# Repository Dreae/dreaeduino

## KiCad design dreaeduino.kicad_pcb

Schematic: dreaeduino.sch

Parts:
C1, C2: 22 pF; C_0805_2012Metric; PartNumber 885012007012
C3, C4: 10uF; C_0805_2012Metric; PartNumber CC0805ZKY5V6BB106
C5: 10uF; C_1210_3225Metric; PartNumber TAJB106K006TNJ
C6: 0.1 uF; C_0805_2012Metric; PartNumber 885012207098
D1: LED; LED_0805_2012Metric_Castellated; PartNumber 150080GS75000
J1, J2, J3, J4: Conn_01x08_Female; PinHeader_1x08_P2.54mm_Vertical
J5: USB_B_Micro; USB_Micro-B_Molex-105017-0001; PartNumber 105017-0001
J6, J7: Conn_02x03_Odd_Even; PinHeader_2x03_P2.54mm_Vertical; PartNumber 61200621621
R1: 10k; R_0805_2012Metric; PartNumber ERJ-6ENF1002V
R2: 220; R_0805_2012Metric; PartNumber CRCW0805220RFKEB
SW1: SW_DIP_x01; SW_SPST_TL3305A; PartNumber TL3305AF160QG
U1: ATxmega32A4U-AU; TQFP-44_10x10mm_P0.8mm; PartNumber ATxmega32A4-AU
U2: TXB0104D; SOIC-14_3.9x8.7mm_P1.27mm; PartNumber TXB0104D
U3: NCP1117ST33T3G; SOT-223; MPN NCP1117ST33T3G; Digi-Key_PN NCP1117ST33T3GOSCT-ND
Y1: 32 MHz; Crystal_SMD_2520-4Pin_2.5x2.0mm; PartNumber FA-20H 32.0000MF20X-K3

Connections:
+5V: C3.1, C5.1, J5.1, J7.2, U2.14, U3.3
/PB0: J1.4, U1.4 (AREFB/PB0)
/PB1: J1.3, U1.5 (PB1)
/PB2: J1.2, U1.6 (PB2)
/PB3: J1.1, U1.7 (PB3)
/PE0: J1.8, U1.28 (PE0)
/PE1: J1.7, U1.29 (PE1)
/PE2: J1.6, U1.32 (PE2)
/PE3: J1.5, U1.33 (PE3)
/Reset: J6.5, R1.2, SW1.2, U1.35 (~RESET~/PDI_CLK), U2.2
GND: C1.2, C2.2, C3.2, C4.2, C5.2, C6.1, J5.5, J6.6, J7.6, R2.1, SW1.1, U1.8 (GND), U1.18 (GND), U1.30 (GND), U1.38 (GND), U2.7, U3.1
unnamed: C1.1, U1.36 (PR0/XTAL2), Y1.1
unnamed: C2.1, U1.37 (PR1/XTAL1), Y1.3
unnamed: D1.1, R2.2
unnamed: J2.1, U1.27 (PD7)
unnamed: J2.2, U1.26 (PD6)
unnamed: J2.3, U1.25 (PD5)
unnamed: J2.4, U1.24 (PD4)
unnamed: J2.5, U1.23 (PD3)
unnamed: J2.6, U1.22 (PD2)
unnamed: J2.7, U1.21 (PD1)
unnamed: J2.8, U1.20 (PD0)
unnamed: J3.1, U1.40 (AREFA/PA0)
unnamed: J3.2, U1.41 (PA1)
unnamed: J3.3, U1.42 (PA2)
unnamed: J3.4, U1.43 (PA3)
unnamed: J3.5, U1.44 (PA4)
unnamed: J3.6, U1.1 (PA5)
unnamed: J3.7, U1.2 (PA6)
unnamed: J3.8, U1.3 (PA7)
unnamed: J4.1, U1.10 (PC0)
unnamed: J4.2, U1.11 (PC1)
unnamed: J4.3, U1.12 (PC2)
unnamed: J4.4, U1.13 (PC3)
unnamed: J4.5, U1.14 (PC4)
unnamed: J4.6, U1.15 (PC5), U2.5
unnamed: J4.7, U1.16 (PC6), U2.4
unnamed: J4.8, U1.17 (PC7), U2.3
unnamed: J6.1, U1.34 (PDI_DATA)
unnamed: J7.1, U2.11
unnamed: J7.3, U2.12
unnamed: J7.4, U2.10
unnamed: J7.5, U2.13
VCC: C4.1, C6.2, D1.2, J6.2, R1.1, U1.9 (VCC), U1.19 (VCC), U1.31 (VCC), U1.39 (AVCC), U2.1, U2.8, U3.2

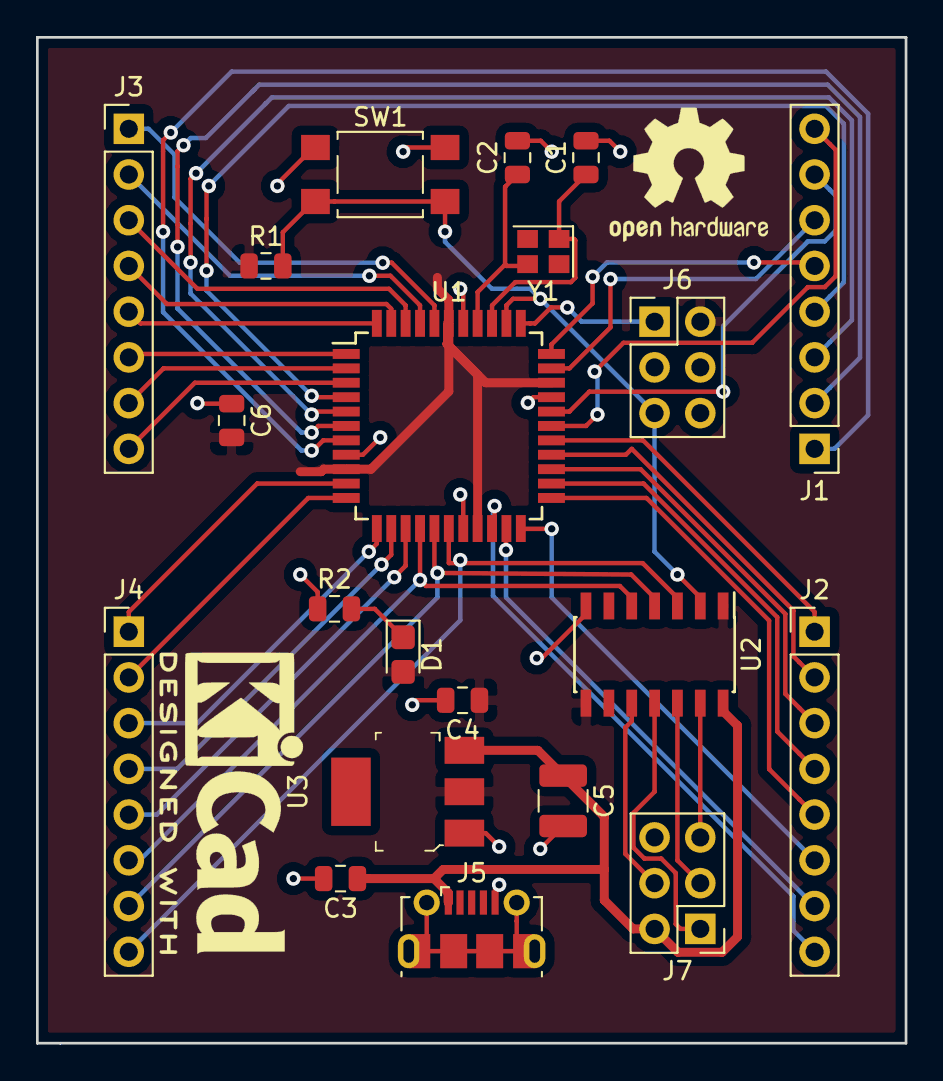
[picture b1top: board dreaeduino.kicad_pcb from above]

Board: 2 copper layers, 48.3 x 55.9 mm, 21 parts (0 on the bottom side), 44 nets.

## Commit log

2019-01-10 initial
2019-01-11 Use better voltage regulator
